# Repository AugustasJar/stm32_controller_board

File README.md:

# stm32_controller_board
Board used for generic robotics control projects

The board uses an STM32F103C6B chip and it has various peripherals:

5-30V to 3.3V LDO,

pn-board L3GD20 gyroscope connected via SPI,

a mount for a NRF24L02 chip to be soldering directly on the board.

The board also has various IO:

Micro USB,

JTAG,

full pinout with screw terminals.

The board has to be programmed with a ST-LINK*

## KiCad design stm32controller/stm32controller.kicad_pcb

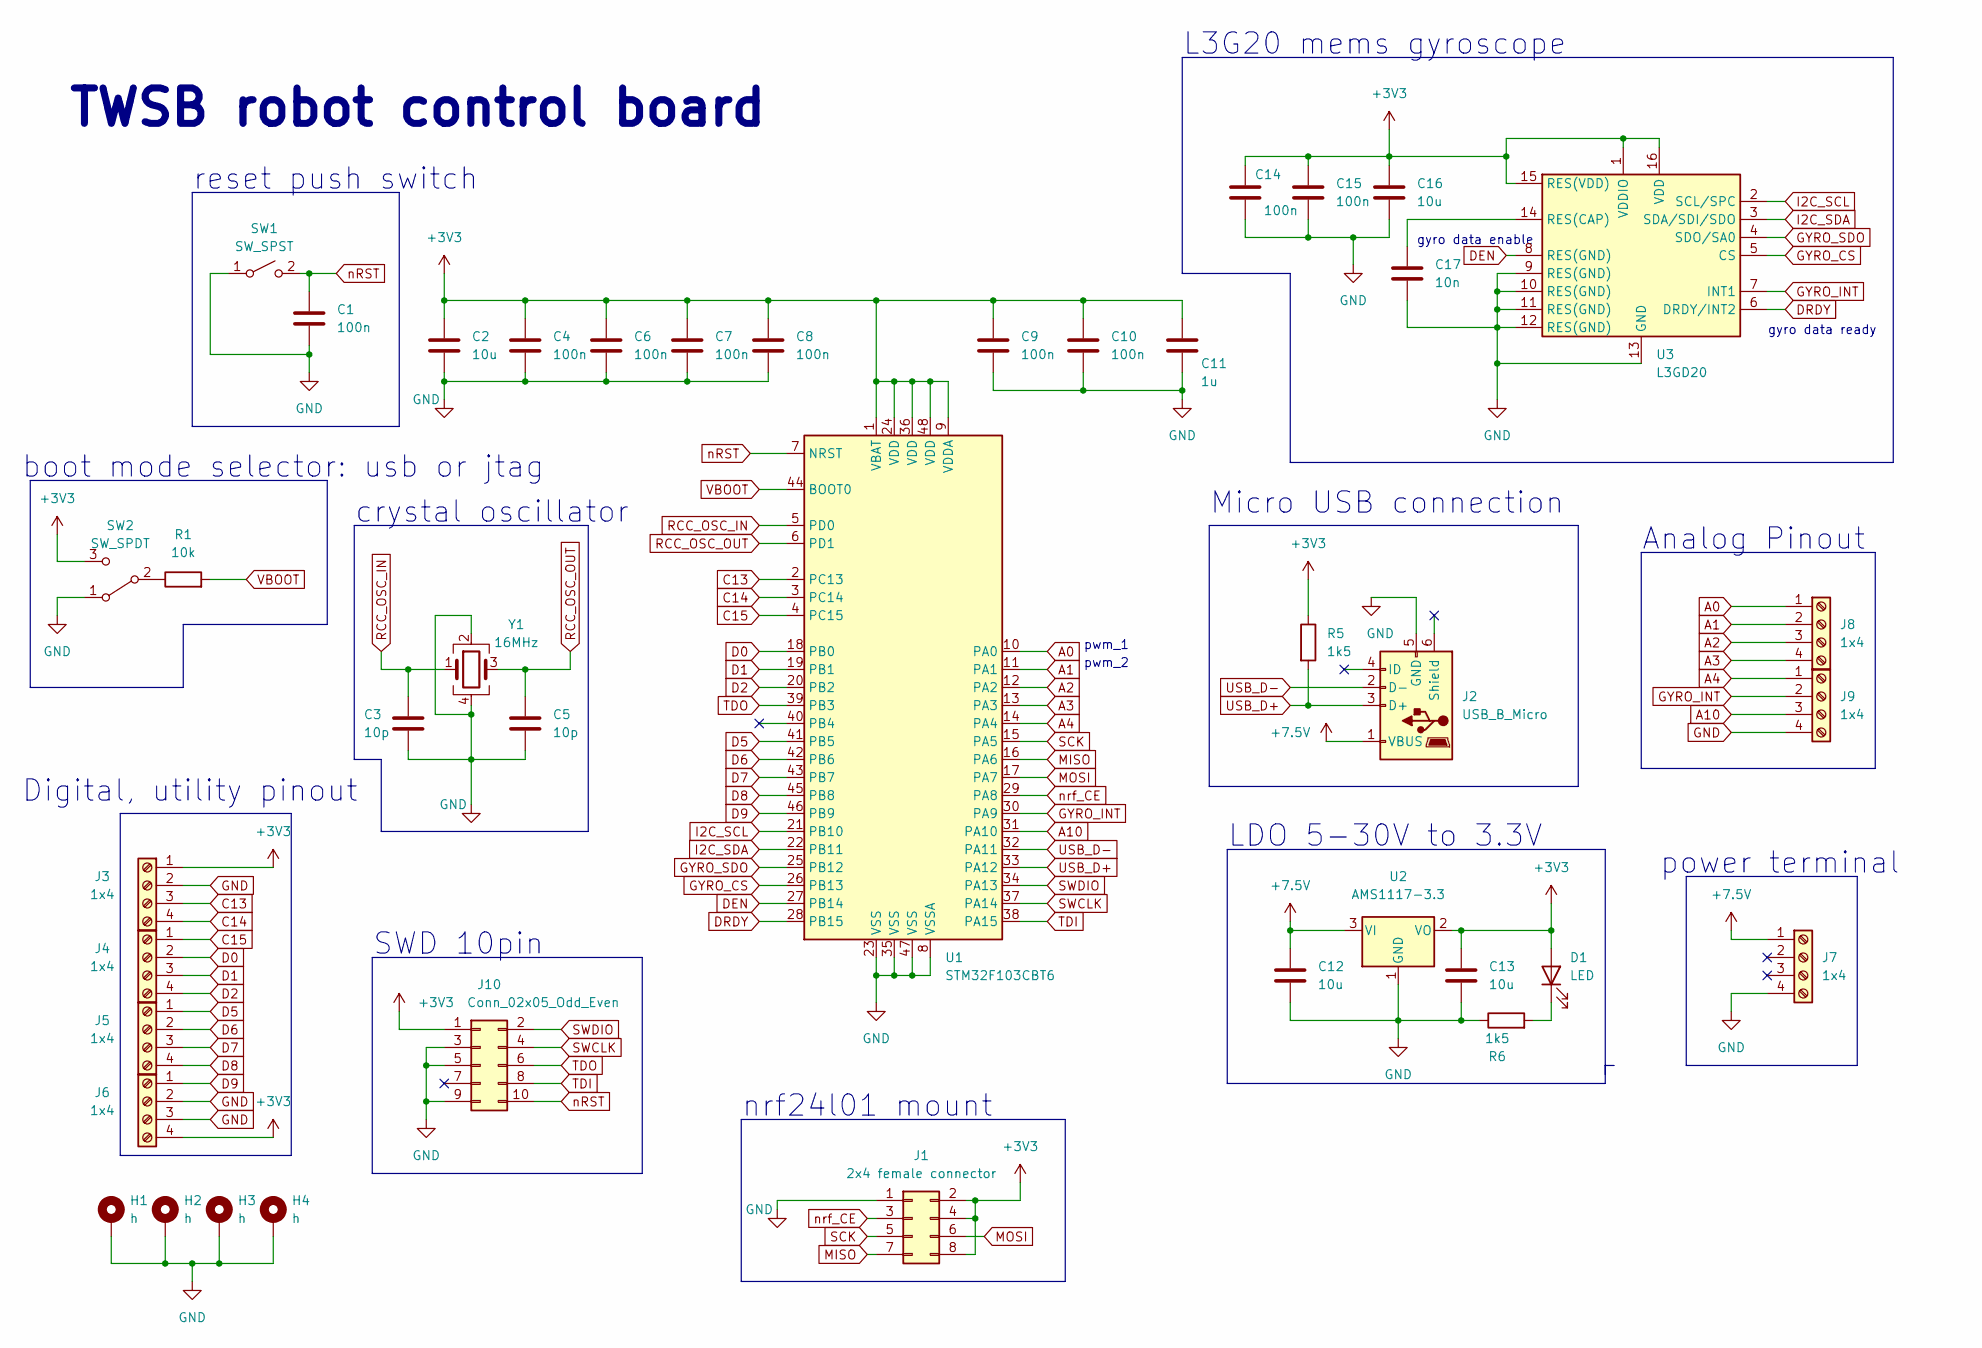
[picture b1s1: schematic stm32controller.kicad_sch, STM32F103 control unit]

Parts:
C1, C4, C6, C7, C8, C9, C10, C14, C15: 100n; C_0805_2012Metric_Pad1.18x1.45mm_HandSolder
C2, C12, C13, C16: 10u; C_1206_3216Metric_Pad1.33x1.80mm_HandSolder
C3, C5: 10p; C_1206_3216Metric_Pad1.33x1.80mm_HandSolder
C11: 1u; C_1206_3216Metric_Pad1.33x1.80mm_HandSolder
C17: 10n; C_1206_3216Metric_Pad1.33x1.80mm_HandSolder
D1: LED; LED_D4.0mm
H1, H2, H3, H4: h; MountingHole_4mm_Pad_TopBottom
J1: 2x4 female connector; PinHeader_2x04_P2.54mm_Vertical
J2: USB_B_Micro; USB_Micro-B_Molex_47346-0001
J3, J4, J5, J6, J7, J8, J9: 1x4; TerminalBlock_Phoenix_MPT-0,5-4-2.54_1x04_P2.54mm_Horizontal
J10: Conn_02x05_Odd_Even; PinHeader_2x05_P2.54mm_Vertical
R1: 10k; R_1206_3216Metric_Pad1.30x1.75mm_HandSolder
R5, R6: 1k5; R_1206_3216Metric_Pad1.30x1.75mm_HandSolder
SW1: SW_SPST; SW_TH_Tactile_Omron_B3F-10xx
SW2: SW_SPDT; SW_DPDT_CK_JS202011JCQN
U1: STM32F103CBT6; LQFP-48_7x7mm_P0.5mm
U2: AMS1117-3.3; SOT-223-3_TabPin2
U3: L3GD20; LGA-16_4x4mm_P0.65mm_LayoutBorder4x4y
Y1: 16MHz; Crystal_SMD_TXC_7M-4Pin_3.2x2.5mm_HandSoldering

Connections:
+3V3: C2.1, C4.1, C6.1, C7.1, C8.1, C9.1, C10.1, C11.1, C13.1, C14.1, C15.1, C16.1, D1.2 (A), J1.2, J1.4, J1.8, J3.1, J6.4, J10.1, R5.1, SW2.3 (C), U1.1 (VBAT), U1.9 (VDDA), U1.24 (VDD), U1.36 (VDD), U1.48 (VDD), U2.2 (VO), U3.1 (VDDIO), U3.15 (RES(VDD)), U3.16 (VDD)
+7.5V: C12.1, J2.1 (VBUS), J7.1, U2.3 (VI)
/RCC_OSC_IN: C3.1, U1.5 (PD0), Y1.1
/RCC_OSC_OUT: C5.1, U1.6 (PD1), Y1.3
/USB_D+: J2.3 (D+), R5.2, U1.33 (PA12)
/USB_D-: J2.2 (D-), U1.32 (PA11)
/variable_boot: R1.2, U1.44 (BOOT0)
A0: J8.1, U1.10 (PA0)
A1: J8.2, U1.11 (PA1)
A2: J8.3, U1.12 (PA2)
A3: J8.4, U1.13 (PA3)
A4: J9.1, U1.14 (PA4)
A10: J9.3, U1.31 (PA10)
C13: J3.3, U1.2 (PC13)
C14: J3.4, U1.3 (PC14)
C15: J4.1, U1.4 (PC15)
D0: J4.2, U1.18 (PB0)
D1: J4.3, U1.19 (PB1)
D2: J4.4, U1.20 (PB2)
D5: J5.1, U1.41 (PB5)
D6: J5.2, U1.42 (PB6)
D7: J5.3, U1.43 (PB7)
D8: J5.4, U1.45 (PB8)
D9: J6.1, U1.46 (PB9)
DEN: U1.27 (PB14), U3.8 (RES(GND))
DRDY: U1.28 (PB15), U3.6 (DRDY/INT2)
GND: C1.2, C2.2, C3.2, C4.2, C5.2, C6.2, C7.2, C8.2, C9.2, C10.2, C11.2, C12.2, C13.2, C14.2, C15.2, C16.2, C17.2, H1.1, H2.1, H3.1, H4.1, J1.1, J2.5 (GND), J3.2, J6.2, J6.3, J7.4, J9.4, J10.3, J10.5, J10.9, R6.1, SW1.1 (A), SW2.1 (A), U1.8 (VSSA), U1.23 (VSS), U1.35 (VSS), U1.47 (VSS), U2.1 (GND), U3.9 (RES(GND)), U3.10 (RES(GND)), U3.11 (RES(GND)), U3.12 (RES(GND)), U3.13 (GND), Y1.2, Y1.4
GYRO_CS: U1.26 (PB13), U3.5 (CS)
GYRO_INT: J9.2, U1.30 (PA9), U3.7 (INT1)
GYRO_SDO: U1.25 (PB12), U3.4 (SDO/SA0)
I2C_SCL: U1.21 (PB10), U3.2 (SCL/SPC)
I2C_SDA: U1.22 (PB11), U3.3 (SDA/SDI/SDO)
MISO: J1.7, U1.16 (PA6)
MOSI: J1.6, U1.17 (PA7)
unnamed: C17.1, U3.14 (RES(CAP))
unnamed: D1.1 (K), R6.2
unnamed: R1.1, SW2.2 (B)
SCK: J1.5, U1.15 (PA5)
SWCLK: J10.4, U1.37 (PA14)
SWDIO: J10.2, U1.34 (PA13)
TDI: J10.8, U1.38 (PA15)
TDO: J10.6, U1.39 (PB3)
nRST: C1.1, J10.10, SW1.2 (B), U1.7 (NRST)
nrf_CE: J1.3, U1.29 (PA8)

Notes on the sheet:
gyro data ready
Analog Pinout
pwm_2
nrf24l01 mount
pwm_1
SWD 10pin
gyro data enable
Micro USB connection
reset push switch
boot mode selector: usb or jtag
TWSB robot control board
LDO 5-30V to 3.3V
Digital, utility pinout
power terminal
L3G20 mems gyroscope
crystal oscillator

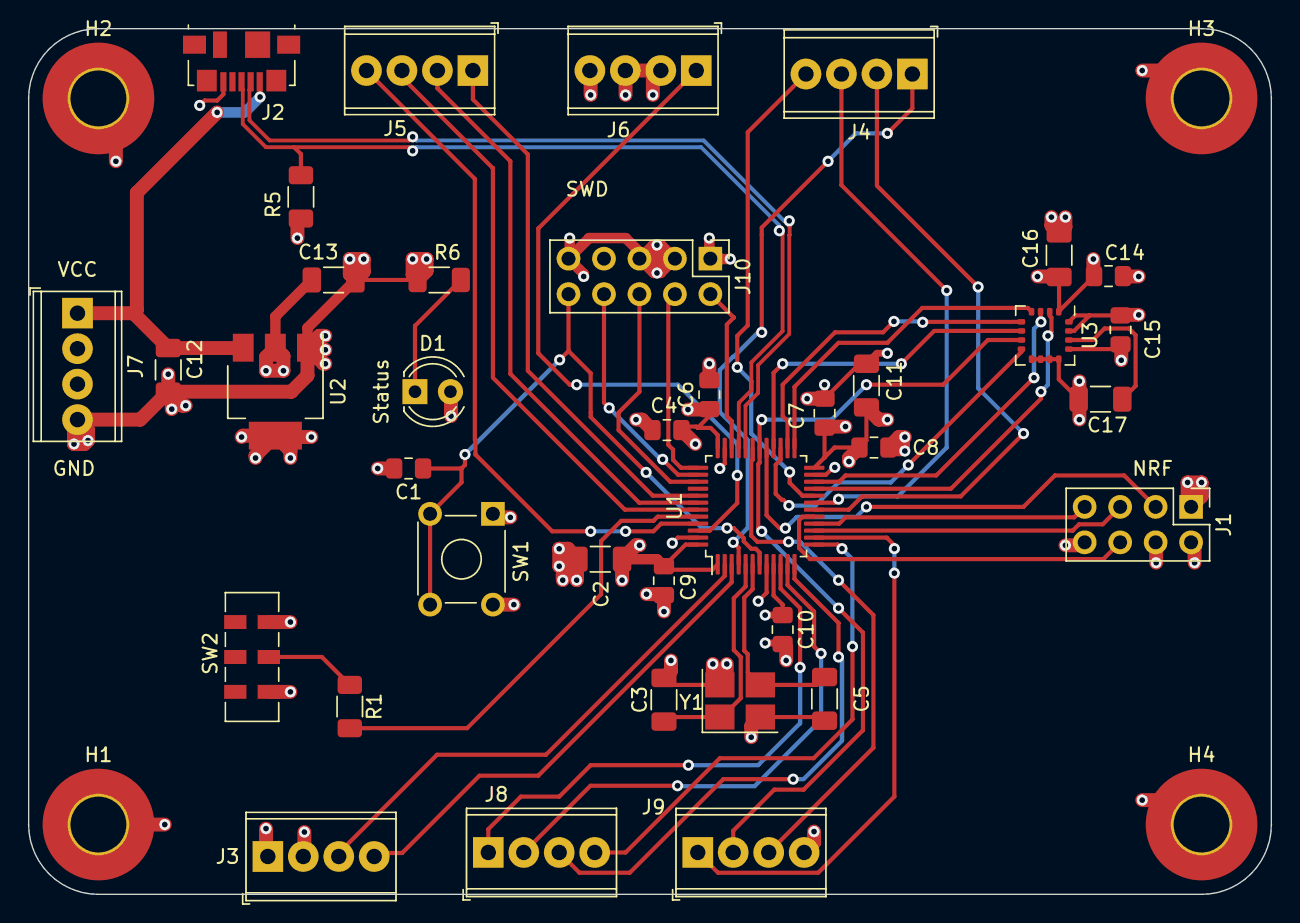
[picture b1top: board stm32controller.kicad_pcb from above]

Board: 4 copper layers, 89.0 x 62.0 mm, 41 parts (0 on the bottom side), 44 nets.

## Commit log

2023-04-02 Kicad upload
